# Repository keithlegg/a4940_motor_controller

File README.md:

# a4940_motor_controller

My attempt to make the highest current motor controller possible. 

Allows for up to 16 through hole N channel mosfets. Only tested up to 8.

Driven by the allegro A4940.

Tested but much more to do 

video of it in action: https://www.youtube.com/watch?v=BzIux2-qr-M

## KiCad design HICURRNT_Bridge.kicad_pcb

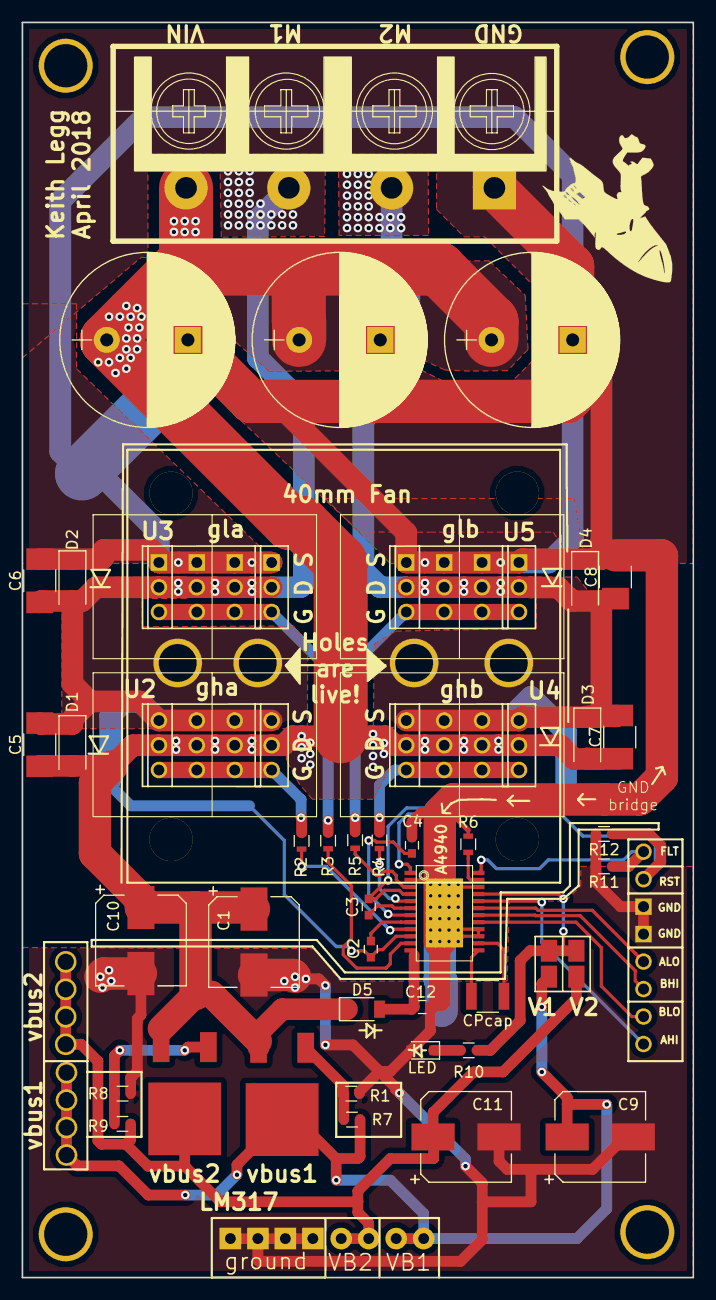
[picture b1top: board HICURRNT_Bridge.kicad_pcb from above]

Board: 2 copper layers, 62.0 x 116.0 mm, 37 parts (0 on the bottom side), 14 nets.

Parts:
C1, C10: CP_Elec_8x5.4
C2, C3, C4, C12: C_0603
C5, C6, C7, C8: C_1210_HandSoldering
C9, C11: pc; CP_Elec_8x5.4
CPcap: C_1210
D1, D2, D3, D4: D_2010
D5: D_1206
LED: D_0805
R1, R6, R7, R8, R9, R10, R11, R12: R_0603
R2, R3, R4, R5: R; R_0603
U2, U3, U4, U5: KL_dual_mosfet_thruhole
vbus1: DPak_TO252AA
vbus2: LM317; DPak_TO252AA

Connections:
/out_a: C2.2, C5.2, C6.1, D1.1, D2.2, U2.3, U3.2
/out_b: C3.2, C7.2, C8.1, D3.1, D4.2, U4.3, U5.2
/vbus1: C9.1, R7.1, vbus1.2
/vbus2: C11.1, R9.1, vbus2.2
/vmot: C1.1, C5.1, C7.1, C10.1, D1.2, D3.2, D5.1, U2.2, U4.2, vbus1.3, vbus2.3
GND: C1.2, C4.1, C6.2, C8.2, C9.2, C10.2, C11.2, C12.1, D2.1, D4.1, LED.2, R1.2, R6.1, R8.2, R11.2, R12.2, U3.3, U5.3
unnamed: C12.2, D5.2
unnamed: LED.1, R10.1
unnamed: R1.1, R7.2, vbus1.1
unnamed: R2.2, U2.1
unnamed: R3.2, U3.1
unnamed: R4.2, U4.1
unnamed: R5.2, U5.1
unnamed: R8.1, R9.2, vbus2.1

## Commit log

2018-12-22 first
2018-12-22 second
2018-12-25 added youtube link
